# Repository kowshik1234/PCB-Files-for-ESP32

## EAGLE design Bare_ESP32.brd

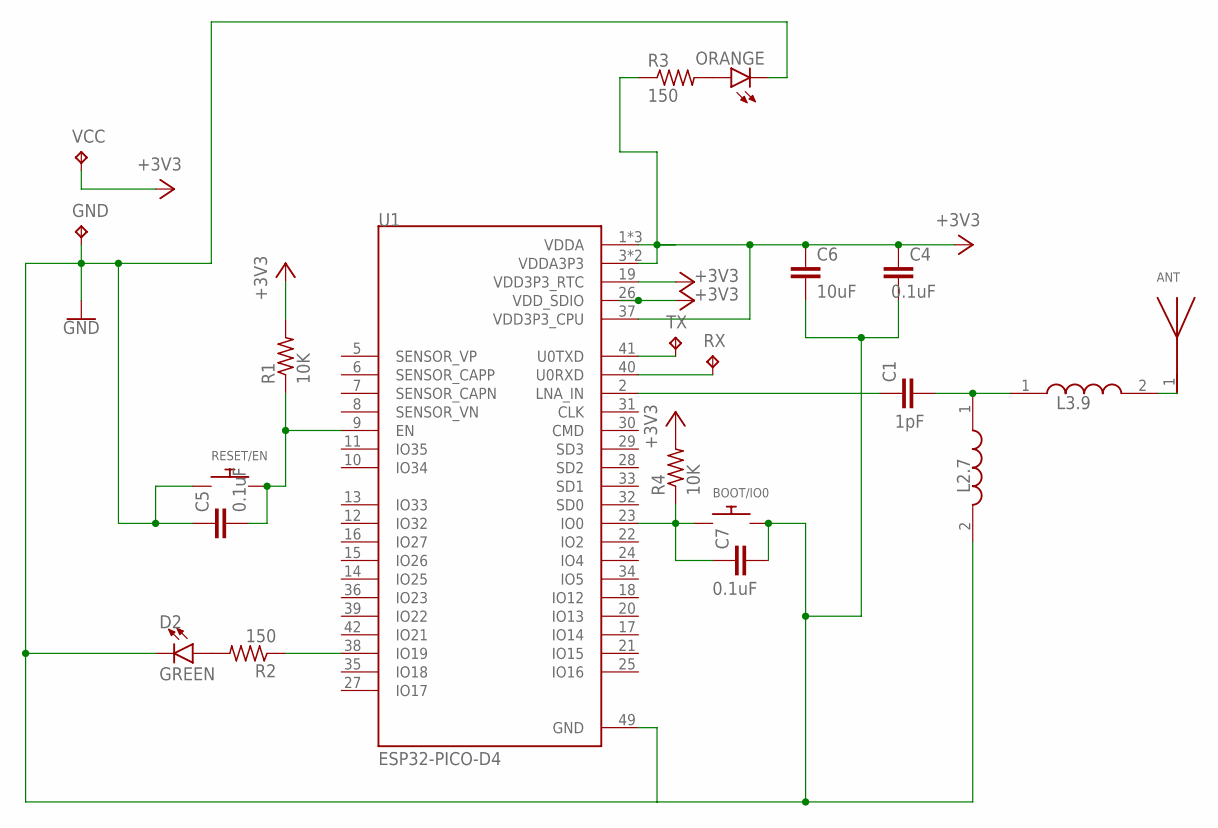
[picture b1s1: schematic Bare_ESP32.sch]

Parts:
ANT: 2450AT18A100E; ANTC3216X140N
BOOT/IO0: SWITCH_PUSHBUTTONEVQ-PE; TACT_PANA-EVQ
C1: 1pF; 0402
C4, C5, C7: 0.1uF; 0402
C6: 10uF; 0402
D2: GREEN; LED-1206
GND: TPTP14SQ; TP14SQ
L2.7: 2.7nH; INDC1005X60N
L3.9: 3.9nH; INDC1005X60N
ORANGE: LED-ORANGE0603; 0603-ORANGE
R1, R4: 10K; R0402
R2, R3: 150; R0402
RESET/EN: SWITCH_PUSHBUTTONEVQ-PE; TACT_PANA-EVQ
RX: TPTP14SQ; TP14SQ
TX: TPTP14SQ; TP14SQ
U1: ESP32-PICO-D4; PQFN50P700X700X104-49N
VCC: TPTP14SQ; TP14SQ

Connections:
+3V3: C4.1, C6.1, R1.2, R3.1, R4.2, U1.1 (VDDA), U1.3 (VDDA3P3), U1.4 (VDDA3P3), U1.19 (VDD3P3_RTC), U1.26 (VDD_SDIO), U1.37 (VDD3P3_CPU), U1.43 (VDDA), U1.46 (VDDA), VCC.TP
GND: BOOT/IO0.P$2, C4.2, C5.1, C6.2, C7.2, D2.C, GND.TP, L2.7.2, ORANGE.C, RESET/EN.P$1, U1.49 (GND)
unnamed: C1.2, L2.7.1, L3.9.1
unnamed: ORANGE.A, R3.2
unnamed: BOOT/IO0.P$1, C7.1, R4.1, U1.23 (IO0)
unnamed: C1.1, U1.2 (LNA_IN)
unnamed: C5.2, R1.1, RESET/EN.P$2, U1.9 (EN)
unnamed: ANT.1, L3.9.2
unnamed: D2.A, R2.2
unnamed: R2.1, U1.38 (IO19)
unnamed: TX.TP, U1.41 (U0TXD)
unnamed: RX.TP, U1.40 (U0RXD)

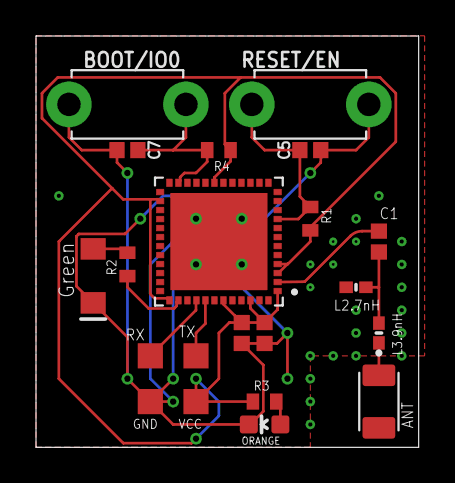
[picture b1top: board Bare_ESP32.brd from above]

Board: 2 copper layers, 21.3 x 22.9 mm, 21 parts (0 on the bottom side), 12 nets.

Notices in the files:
parts and their libraries:
SparkFun-Capacitors: Licensing: Creative Commons ShareAlike 4.0 International - https://creativecommons.org/licenses/by-sa/4.0
